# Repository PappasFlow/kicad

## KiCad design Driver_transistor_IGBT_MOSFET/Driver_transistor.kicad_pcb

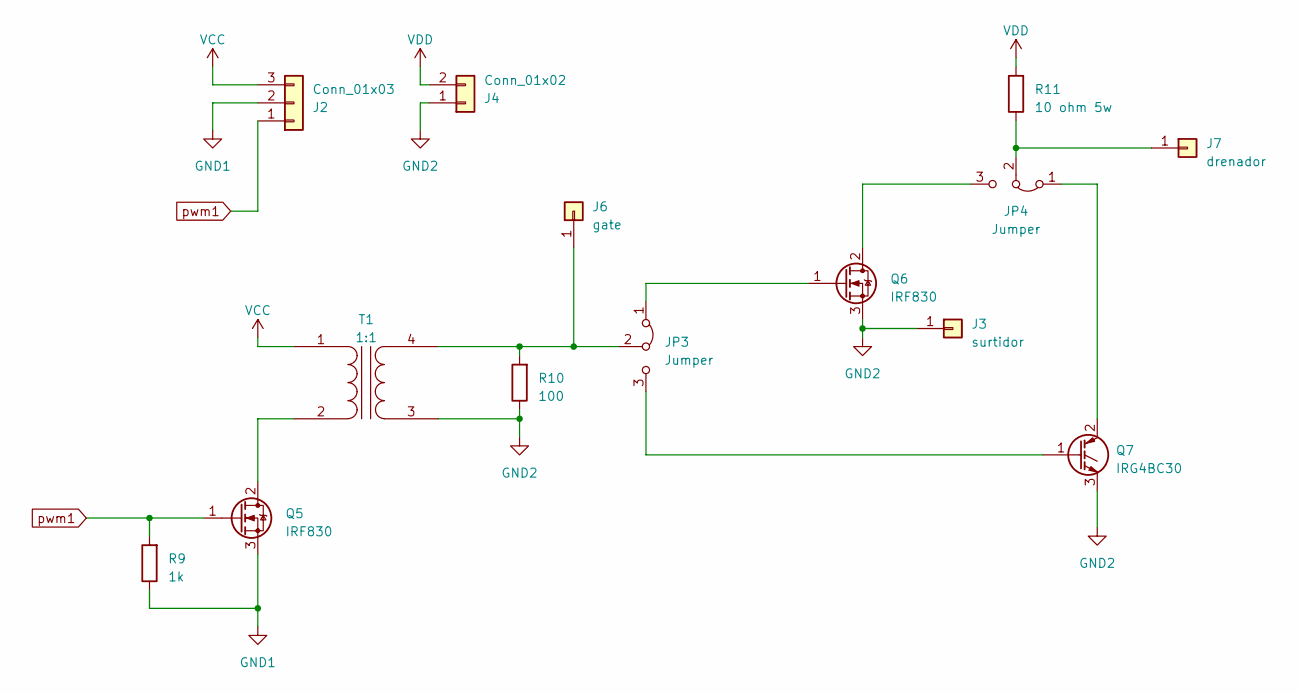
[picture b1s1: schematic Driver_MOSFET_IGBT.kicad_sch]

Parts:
J2: Conn_01x03; Altech_AK300_1x03_P5.00mm_45-Degree
J3: surtidor; PinHeader_1x01_P2.00mm_Vertical
J4: Conn_01x02; Altech_AK300_1x02_P5.00mm_45-Degree
J6: gate; PinHeader_1x01_P2.00mm_Vertical
J7: drenador; PinHeader_1x01_P2.00mm_Vertical
JP3, JP4: Jumper; PinHeader_1x03_P2.00mm_Vertical
Q5, Q6: IRF830; TO-220-3_Vertical
Q7: IRG4BC30; TO-247-3_Vertical
R9: 1k; R_Axial_DIN0207_L6.3mm_D2.5mm_P7.62mm_Horizontal
R10: 100; R_Axial_DIN0207_L6.3mm_D2.5mm_P7.62mm_Horizontal
R11: 10 ohm 5w; R_Axial_Power_L20.0mm_W6.4mm_P22.40mm
T1: 1:1; Transformer_Driver_IGBT_MOSFET

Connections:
GND1: Q5.3 (S), R9.1; also elsewhere on the board
GND2: J3.1, J4.1, Q6.3 (S), Q7.3 (E), R10.1, T1.3 (SA)
unnamed: J6.1, JP3.2 (C), R10.2, T1.4 (SB)
unnamed: J7.1, JP4.2 (C), R11.1
unnamed: JP3.1 (A), Q6.1 (G)
unnamed: JP3.3 (B), Q7.1 (G)
unnamed: JP4.1 (A), Q7.2 (C)
unnamed: JP4.3 (B), Q6.2 (D)
unnamed: Q5.2 (D), T1.2 (AB)
VCC: T1.1 (AA); also elsewhere on the board
VDD: J4.2, R11.2
pwm1: Q5.1 (G), R9.2; also elsewhere on the board

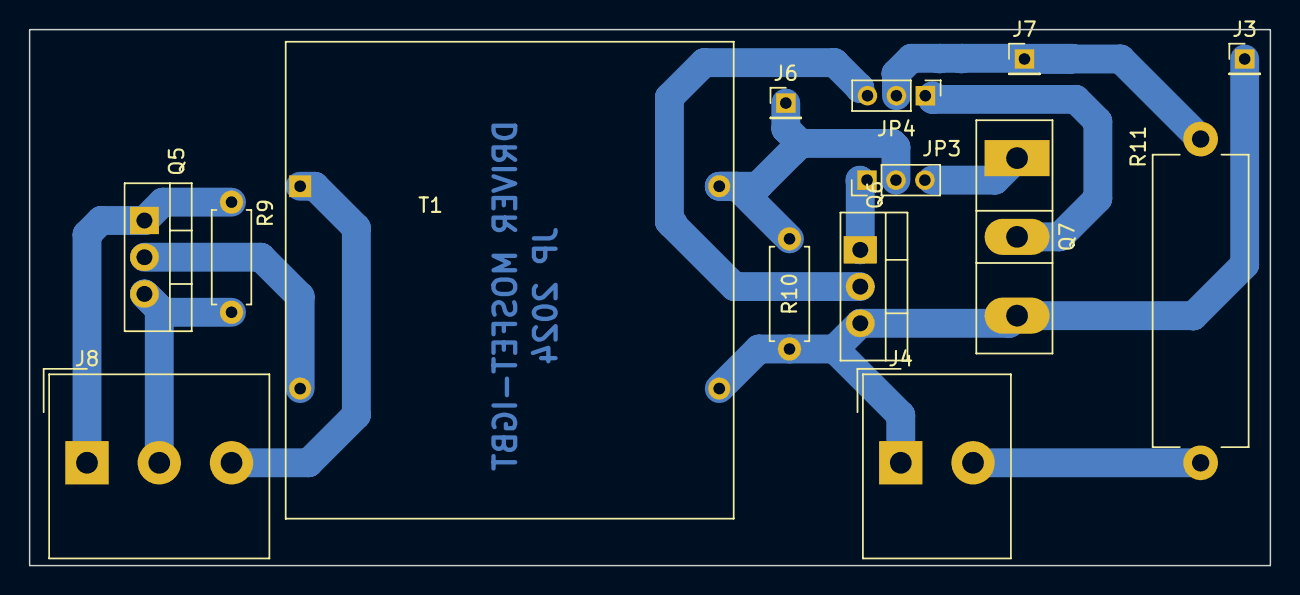
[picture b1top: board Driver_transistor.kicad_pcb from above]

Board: 2 copper layers, 85.9 x 37.1 mm, 14 parts (0 on the bottom side), 12 nets.

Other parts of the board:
J8: Conn_01x03; Altech_AK300_1x03_P5.00mm_45-Degree

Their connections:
GND1: J8.2; also elsewhere on the board
VCC: J8.3; also elsewhere on the board
pwm1: J8.1; also elsewhere on the board

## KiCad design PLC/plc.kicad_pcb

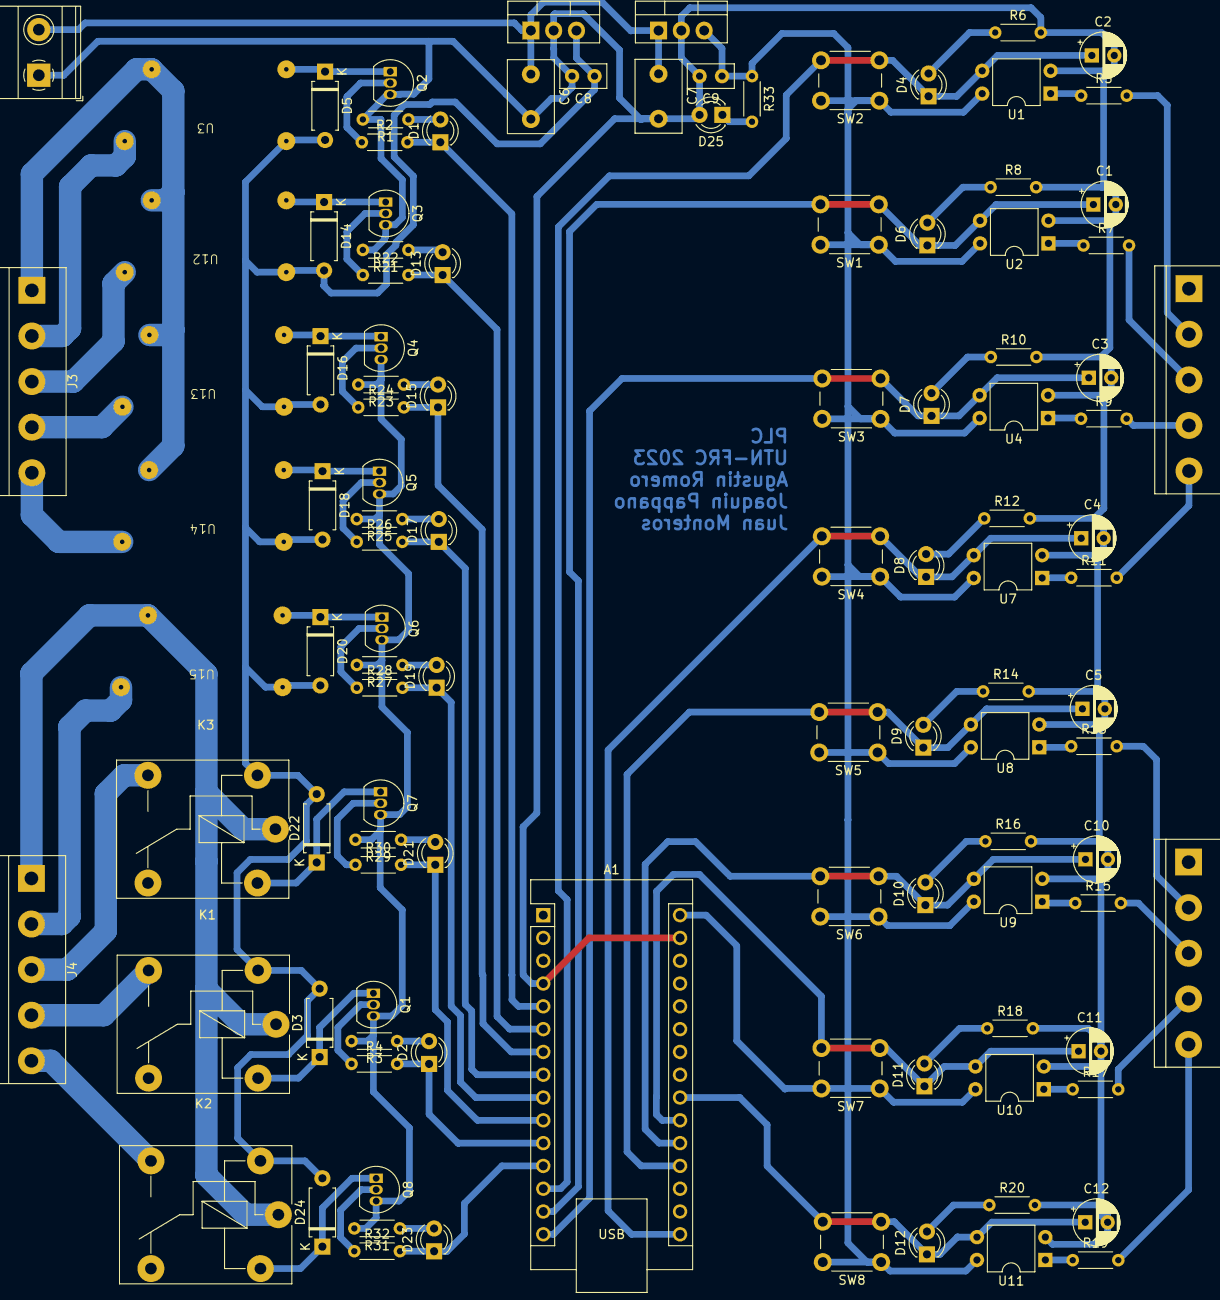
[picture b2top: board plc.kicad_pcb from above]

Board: 2 copper layers, 110 parts (0 on the bottom side), 79 nets.

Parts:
A1: Arduino_Nano_v3.x; Arduino_Nano
C1, C2, C3, C4, C5, C10, C11, C12: 1uF; CP_Radial_D5.0mm_P2.50mm
C6, C7: 0.33uF1; C_Disc_D8.0mm_W5.0mm_P5.00mm
C8, C9: 0.1uF1; C_Disc_D5.0mm_W2.5mm_P2.50mm
D1, D2, D4, D6, D7, D8, D9, D10, D11, D12, D13, D15, D17, D19, D21, D23, D25: LED; LED_D3.0mm
D3, D5, D14, D16, D18, D20, D22, D24: 1N4007; D_A-405_P7.62mm_Horizontal
J1: Conn_in24_0; TerminalBlock_bornier-5_P5.08mm
J2: Conn_in24_1; TerminalBlock_bornier-5_P5.08mm
J3: Conn_rele_0; TerminalBlock_bornier-5_P5.08mm
J4: Conn_rele_1; TerminalBlock_bornier-5_P5.08mm
K1, K2, K3: FINDER-36.11; Relay_SPDT_Finder_36.11
Q1, Q2, Q3, Q4, Q5, Q6, Q7, Q8: BC557; TO-92_Inline
R1, R3, R21, R23, R25, R27, R29, R31: 1K; R_Axial_DIN0204_L3.6mm_D1.6mm_P5.08mm_Horizontal
R2, R4, R22, R24, R26, R28, R30, R32: 10k; R_Axial_DIN0204_L3.6mm_D1.6mm_P5.08mm_Horizontal
R5, R6, R7, R8, R9, R10, R11, R12, R13, R14, R15, R16, R17, R18, R19, R20, R33: 1k; R_Axial_DIN0204_L3.6mm_D1.6mm_P5.08mm_Horizontal
SW1, SW2, SW3, SW4, SW5, SW6, SW7, SW8: SW_PUSH; SW_PUSH_6mm_H5mm
U1, U2, U4, U7, U8, U9, U10, U11: PC817; DIP-4_W7.62mm
U3, U12, U13, U14, U15: RSEIV-JMU
U5: LM7812_TO220; TO-220-3_Vertical
U6: LM7805_TO220; TO-220-3_Vertical
con2: Vin; TerminalBlock_Phoenix_MKDS-1,5-2-5.08_1x02_P5.08mm_Horizont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

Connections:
+5V: A1.30 (VIN), C9.1, R33.1, SW1.1, SW2.1, SW3.1, SW4.1, SW5.1, SW6.1, SW7.1, SW8.1, U1.4, U2.4, U4.4, U6.3 (VO), U7.4, U8.4, U9.4, U10.4, U11.4
+12V: C8.1, D3.2 (K), D5.2 (K), D14.2 (K), D16.2 (K), D18.2 (K), D20.2 (K), D22.2 (K), D24.2 (K), K1.A1, K2.A1, K3.A1, U3.1, U5.3 (VO), U12.1, U13.1, U14.1, U15.1
GND: A1.4 (GND), A1.29 (GND), C1.2, C2.2, C3.2, C4.2, C5.2, C6.2, C7.2, C8.2, C9.2, C10.2, C11.2, C12.2, D25.2 (K), J1.1, J2.1, Q1.3 (E), Q2.3 (E), Q3.3 (E), Q4.3 (E), Q5.3 (E), Q6.3 (E), Q7.3 (E), Q8.3 (E), R1.2, R3.2, R6.2, R8.2, R10.2, R12.2, R14.2, R16.2, R18.2, R20.2, R21.2, R23.2, R25.2, R27.2, R29.2, R31.2, U1.2, U2.2, U4.2, U5.2 (GND), U6.2 (GND), U7.2, U8.2, U9.2, U10.2, U11.2, con2.1
unnamed: D1.2 (K), R1.1
unnamed: D2.2 (K), R3.1
unnamed: D3.1 (A), K1.A2, Q1.1 (C)
unnamed: D4.2 (K), R6.1
unnamed: D5.1 (A), Q2.1 (C), U3.2
unnamed: D6.2 (K), R8.1
unnamed: D7.2 (K), R10.1
unnamed: D8.2 (K), R12.1
unnamed: D9.2 (K), R14.1
unnamed: D10.2 (K), R16.1
unnamed: D11.2 (K), R18.1
unnamed: D12.2 (K), R20.1
unnamed: D13.2 (K), R21.1
unnamed: D14.1 (A), Q3.1 (C), U12.2
unnamed: D15.2 (K), R23.1
unnamed: D16.1 (A), Q4.1 (C), U13.2
unnamed: D17.2 (K), R25.1
unnamed: D18.1 (A), Q5.1 (C), U14.2
unnamed: D19.2 (K), R27.1
unnamed: D20.1 (A), Q6.1 (C), U15.2
unnamed: D21.2 (K), R29.1
unnamed: D22.1 (A), K3.A2, Q7.1 (C)
unnamed: D23.2 (K), R31.1
unnamed: D24.1 (A), K2.A2, Q8.1 (C)
unnamed: D25.1 (A), R33.2
unnamed: Q1.2 (B), R4.1
unnamed: Q2.2 (B), R2.1
unnamed: Q3.2 (B), R22.1
unnamed: Q4.2 (B), R24.1
unnamed: Q5.2 (B), R26.1
unnamed: Q6.2 (B), R28.1
unnamed: Q7.2 (B), R30.1
unnamed: Q8.2 (B), R32.1
unnamed: R5.1, U1.1
unnamed: R7.1, U2.1
unnamed: R9.1, U4.1
unnamed: R11.1, U7.1
unnamed: R13.1, U8.1
unnamed: R15.1, U9.1
unnamed: R17.1, U10.1
unnamed: R19.1, U11.1
Vin: C6.1, C7.1, U5.1 (VI), U6.1 (VI), con2.2 (PM)
in24_0: J1.2, R5.2
in24_1: J1.3, R7.2
in24_2: J1.4, R9.2
in24_3: J1.5, R11.2
in24_4: J2.2, R13.2
in24_5: J2.3, R15.2
in24_6: J2.4, R17.2
in24_7: J2.5, R19.2
in_0: A1.13 (D10), C2.1, D4.1 (A), SW2.2, U1.3
in_1: A1.14 (D11), C1.1, D6.1 (A), SW1.2, U2.3
in_2: A1.15 (D12), C3.1, D7.1 (A), SW3.2, U4.3
in_3: A1.16 (D13), C4.1, D8.1 (A), SW4.2, U7.3
in_4: A1.19 (A0), C5.1, D9.1 (A), SW5.2, U8.3
in_5: A1.20 (A1), C10.1, D10.1 (A), SW6.2, U9.3
in_6: A1.21 (A2), C11.1, D11.1 (A), SW7.2, U10.3
in_7: A1.22 (A3), C12.1, D12.1 (A), SW8.2, U11.3
outR_0: J3.2, U3.3
outR_1: J3.3, U12.3
outR_2: J3.4, U13.3
outR_3: J3.5, U14.3
outR_4: J4.2, U15.3
outR_5: J4.3, K3.14
outR_6: J4.4, K1.14
outR_7: J4.5, K2.14
out_0: A1.5 (D2), D1.1 (A), R2.2
out_1: A1.6 (D3), D13.1 (A), R22.2
out_2: A1.7 (D4), D15.1 (A), R24.2
out_3: A1.8 (D5), D17.1 (A), R26.2
out_4: A1.9 (D6), D19.1 (A), R28.2
out_5: A1.10 (D7), D21.1 (A), R30.2
out_6: A1.11 (D8), D2.1 (A), R4.2
out_7: A1.12 (D9), D23.1 (A), R32.2
pwr_R_0: J3.1, U3.4, U12.4, U13.4, U14.4
pwr_R_1: J4.1, K1.11, K2.11, K3.11, U15.4

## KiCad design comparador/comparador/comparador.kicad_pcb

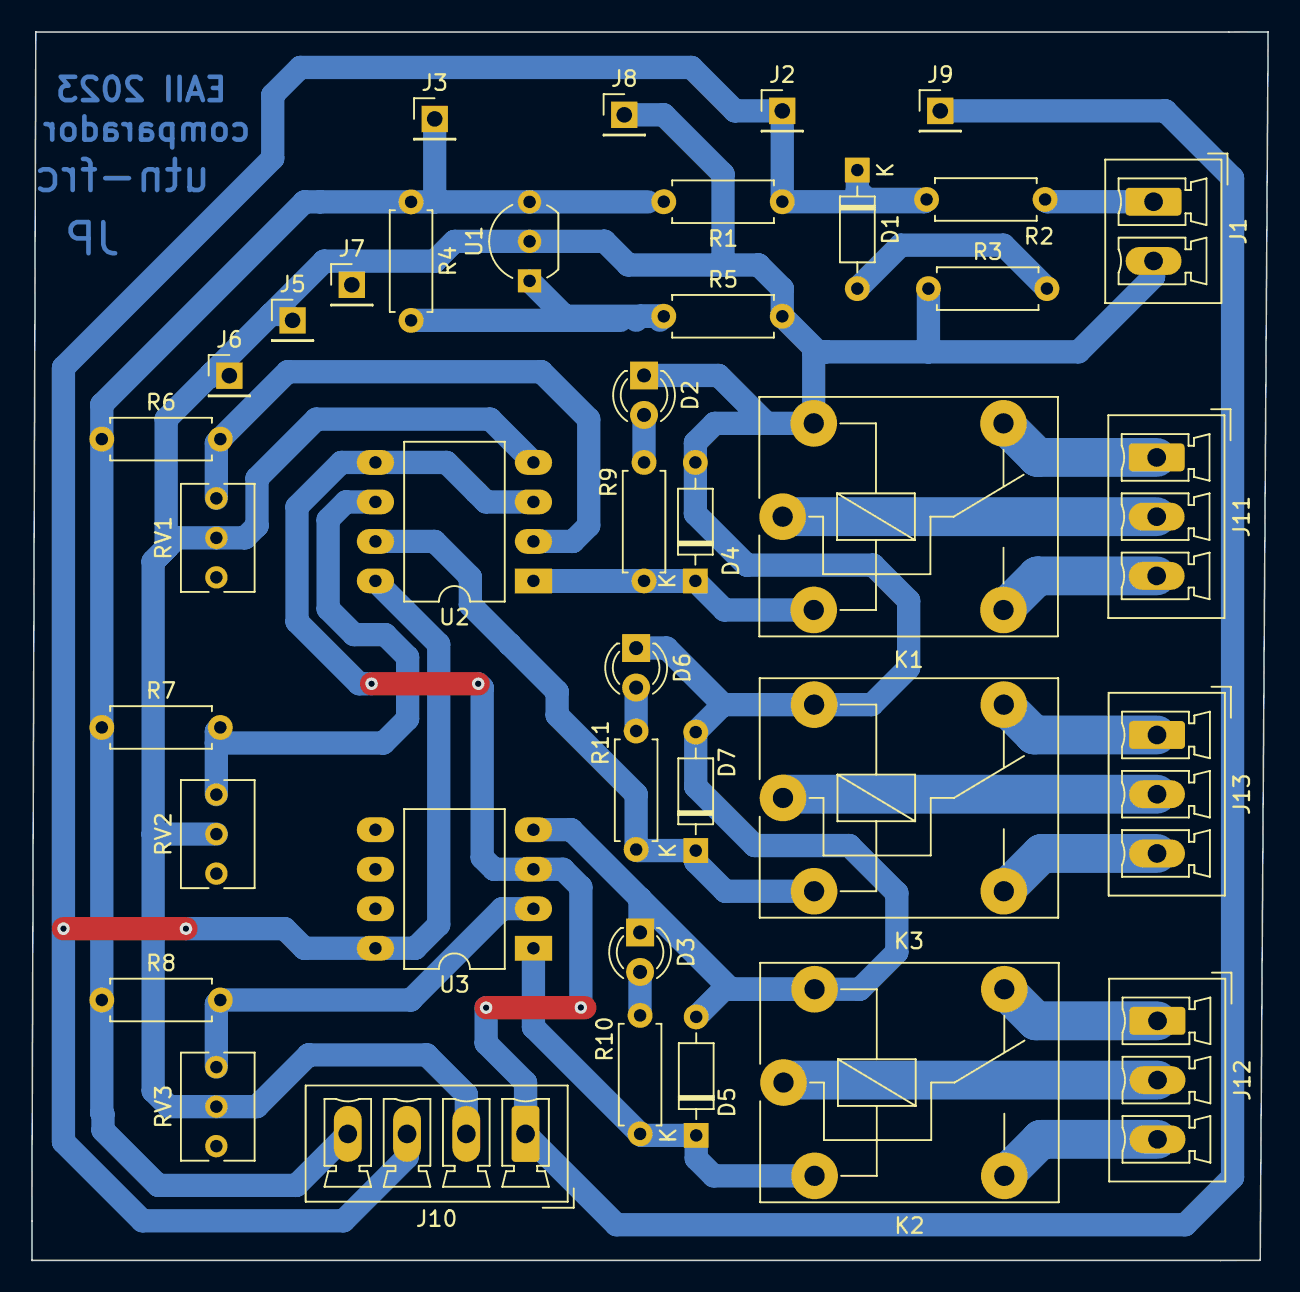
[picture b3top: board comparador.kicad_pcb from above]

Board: 2 copper layers, 79.5 x 79.0 mm, 39 parts (0 on the bottom side), 25 nets.

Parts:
D1: D_Zener; D_DO-35_SOD27_P7.62mm_Horizontal
D2, D3, D6: LED; LED_D3.0mm
D4, D5, D7: D; D_DO-35_SOD27_P7.62mm_Horizontal
J1: alimentacion; PhoenixContact_MCV_1,5_2-G-3.81_1x02_P3.81mm_Vertical
J2: +15; PinHeader_1x01_P2.54mm_Vertical
J3: +5; PinHeader_1x01_P2.54mm_Vertical
J5, J6, J7, J8: GND; PinHeader_1x01_P2.54mm_Vertical
J9: sensor; PinHeader_1x01_P2.54mm_Vertical
J10: exp; PhoenixContact_MCV_1,5_4-G-3.81_1x04_P3.81mm_Vertical
J11, J12, J13: out; PhoenixContact_MCV_1,5_3-G-3.81_1x03_P3.81mm_Vertical
K1, K2, K3: FINDER-36.11; Relay_SPDT_Finder_36.11
R1, R2, R3, R4, R5, R9, R10, R11: R; R_Axial_DIN0207_L6.3mm_D2.5mm_P7.62mm_Horizontal
R6, R7, R8: 1k; R_Axial_DIN0207_L6.3mm_D2.5mm_P7.62mm_Horizontal
RV1, RV2, RV3: 10K; Potentiometer_Bourns_3266Y_Vertical
U1: TL431LP; TO-92_Inline_Wide
U2, U3: TL082; DIP-8_W10.16mm_LongPads

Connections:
+5V: J3.1, J10.4, R1.2, R4.1, R6.1, R7.1, R8.1, U1.3 (K)
+15V: D1.1 (K), J2.1, J10.3, R1.1, R2.2, U2.8 (V+), U3.8 (V+)
GND: D2.1 (K), D3.1 (K), D4.2 (A), D5.2 (A), D6.1 (K), D7.2 (A), J1.2, J5.1, J6.1, J7.1, J8.1, J10.2, K1.A2, K2.A2, K3.A2, R3.1, R5.2, RV1.2, RV2.2, RV3.2, U1.2 (A), U2.4 (V-), U3.4 (V-)
unnamed: D1.2 (A), R3.2
unnamed: D2.2 (A), R9.1
unnamed: D3.2 (A), R10.1
unnamed: D4.1 (K), K1.A1, R9.2, U2.1
unnamed: D5.1 (K), K2.A1, R10.2, U3.1
unnamed: D6.2 (A), R11.1
unnamed: D7.1 (K), K3.A1, R11.2, U2.7
unnamed: J1.1, R2.1
unnamed: J11.1, K1.12
unnamed: J11.2, K1.11
unnamed: J11.3, K1.14
unnamed: J12.1, K2.12
unnamed: J12.2, K2.11
unnamed: J12.3, K2.14
unnamed: J13.1, K3.12
unnamed: J13.2, K3.11
unnamed: J13.3, K3.14
unnamed: R4.2, R5.1, U1.1 (REF)
ldr: J9.1, J10.1, U2.3 (+), U2.5 (+), U3.3 (+)
ref1: R6.2, RV1.1, U2.2 (-)
ref2: R7.2, RV2.1, U2.6 (-)
ref3: R8.2, RV3.1, U3.2 (-)

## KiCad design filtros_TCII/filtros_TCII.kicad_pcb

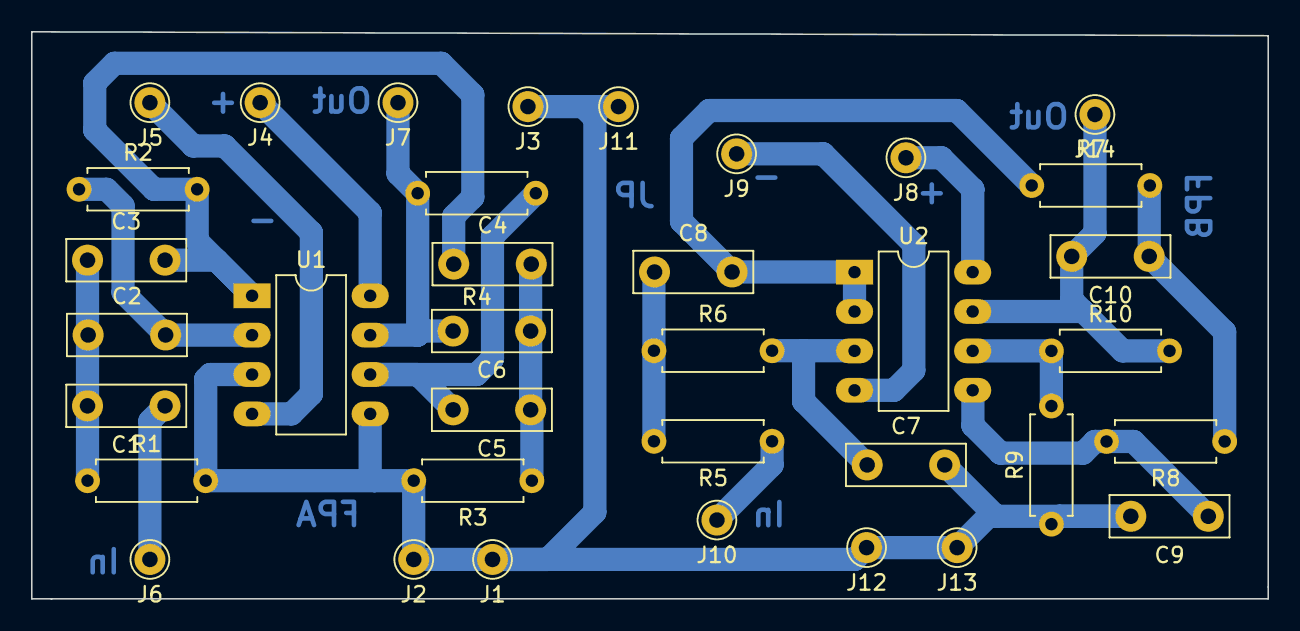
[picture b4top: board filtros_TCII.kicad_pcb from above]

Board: 2 copper layers, 79.8 x 36.6 mm, 36 parts (0 on the bottom side), 20 nets.

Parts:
C1, C2, C3, C4, C5, C6, C7, C8, C9, C10: C; C_Disc_D7.5mm_W2.5mm_P5.00mm
J1, J2, J3, J11, J12, J13: gnd; Pin_D1.0mm_L10.0mm
J4, J8: +15; Pin_D1.0mm_L10.0mm
J5, J9: -15; Pin_D1.0mm_L10.0mm
J6: in_FPA; Pin_D1.0mm_L10.0mm
J7: out_FPA; Pin_D1.0mm_L10.0mm
J10: in_FPB; Pin_D1.0mm_L10.0mm
J14: out_FPB; Pin_D1.0mm_L10.0mm
R1, R2, R3, R4, R5, R6, R7, R8, R9, R10: R; R_Axial_DIN0207_L6.3mm_D2.5mm_P7.62mm_Horizontal
U1, U2: TL082; DIP-8_W7.62mm_LongPads

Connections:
GND: C7.2, C9.2, J1.1, J2.1, J3.1, J11.1, J12.1, J13.1, R1.2, R3.2, R9.1, U1.3 (+), U1.5 (+)
unnamed: C1.2, C2.1, C3.1, R1.1
unnamed: C3.2, C4.1, R2.2, U1.1
unnamed: C4.2, C5.1, C6.1, R3.1
unnamed: C8.1, R5.2, R6.1
unnamed: C10.1, R7.2, R8.1
unnamed: J4.1, U1.8 (V+)
unnamed: J5.1, U1.4 (V-)
unnamed: C1.1, J6.1
unnamed: C6.2, J7.1, R4.2, U1.7
unnamed: J8.1, U2.8 (V+)
unnamed: J9.1, U2.4 (V-)
unnamed: J10.1, R5.1
unnamed: C10.2, J14.1, R10.2, U2.7
unnamed: C2.2, R2.1, U1.2 (-)
unnamed: C5.2, R4.1, U1.6 (-)
unnamed: C7.1, R6.2, U2.3 (+)
unnamed: C8.2, R7.1, U2.1, U2.2 (-)
unnamed: C9.1, R8.2, U2.5 (+)
unnamed: R9.2, R10.1, U2.6 (-)

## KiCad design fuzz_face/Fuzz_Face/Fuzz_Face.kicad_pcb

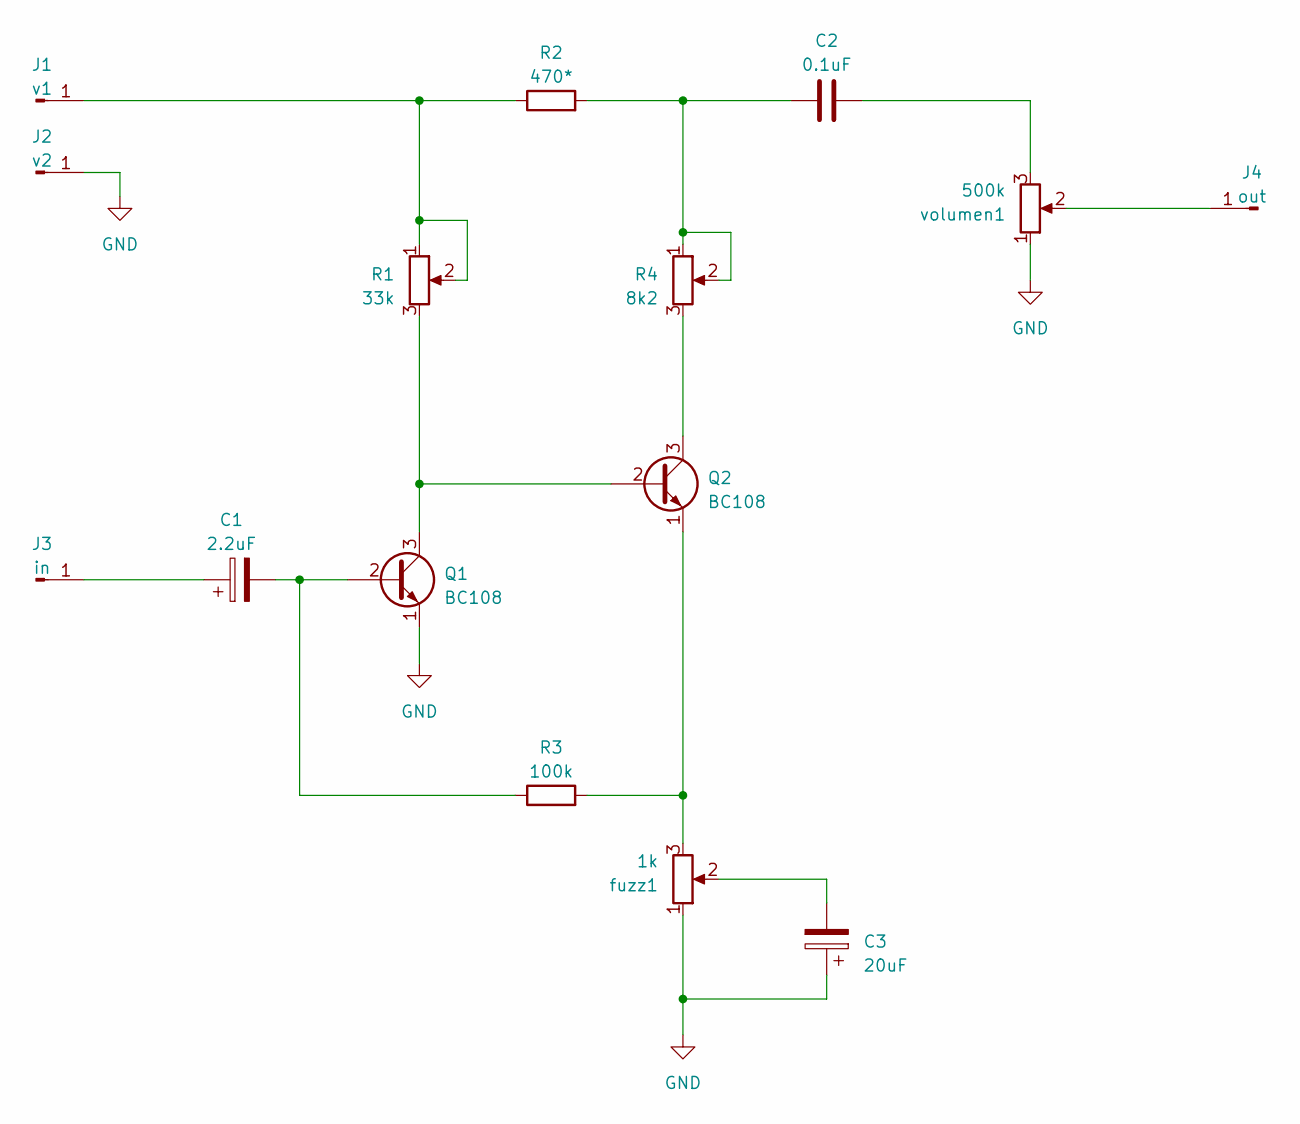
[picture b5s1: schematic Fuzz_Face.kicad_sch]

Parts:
C1: 2.2uF; CP_Radial_D8.0mm_P5.00mm
C2: 0.1uF; CP_Radial_D8.0mm_P5.00mm
C3: 20uF; CP_Radial_D8.0mm_P5.00mm
J1: v1; Pin_D1.3mm_L11.0mm
J2: v2; Pin_D1.3mm_L11.0mm
J3: in; Pin_D1.3mm_L11.0mm
J4: out; Pin_D1.3mm_L11.0mm
Q1, Q2: BC108; TO-18-3
R1: 33k; Potentiometer_Bourns_3266Y_Vertical
R2: 470*; R_Axial_DIN0207_L6.3mm_D2.5mm_P7.62mm_Horizontal
R3: 100k; R_Axial_DIN0207_L6.3mm_D2.5mm_P7.62mm_Horizontal
R4: 8k2; Potentiometer_Bourns_3266Y_Vertical
fuzz1: 1k; Potentiometer_Alps_RK163_Single_Horizontal
volumen1: 500k; Potentiometer_Alps_RK163_Single_Horizontal

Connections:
GND: C3.1, J2.1, Q1.1 (E), fuzz1.1, volumen1.1
unnamed: C2.1, R2.2, R4.1, R4.2
unnamed: C2.2, volumen1.3
unnamed: C3.2, fuzz1.2
unnamed: J1.1, R1.1, R1.2, R2.1
unnamed: C1.1, J3.1
unnamed: J4.1, volumen1.2
unnamed: C1.2, Q1.2 (B), R3.1
unnamed: Q1.3 (C), Q2.2 (B), R1.3
unnamed: Q2.3 (C), R4.3
unnamed: Q2.1 (E), R3.2, fuzz1.3

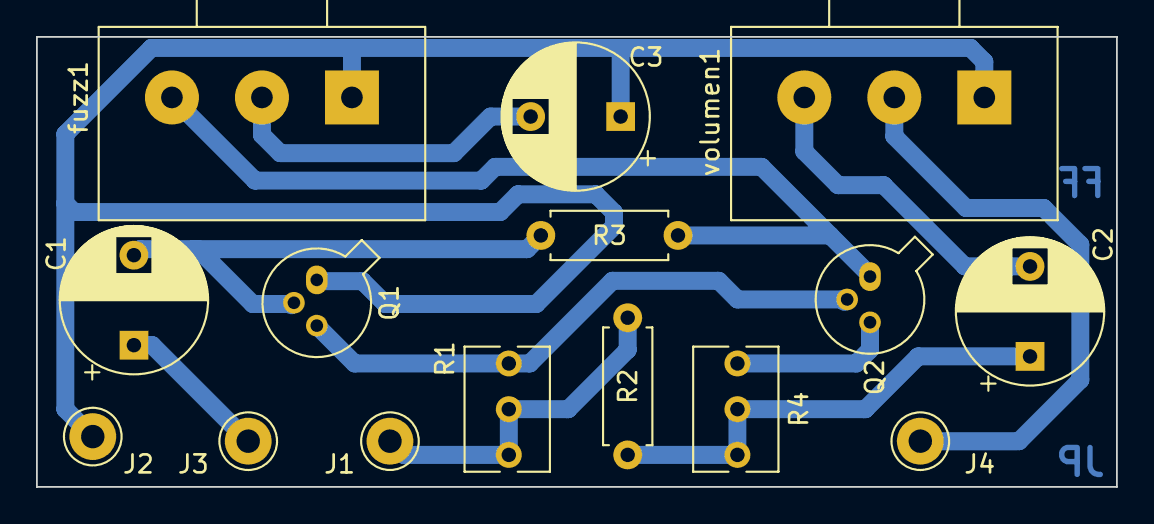
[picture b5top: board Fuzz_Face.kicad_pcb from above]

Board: 2 copper layers, 60.0 x 25.0 mm, 15 parts (0 on the bottom side), 11 nets.

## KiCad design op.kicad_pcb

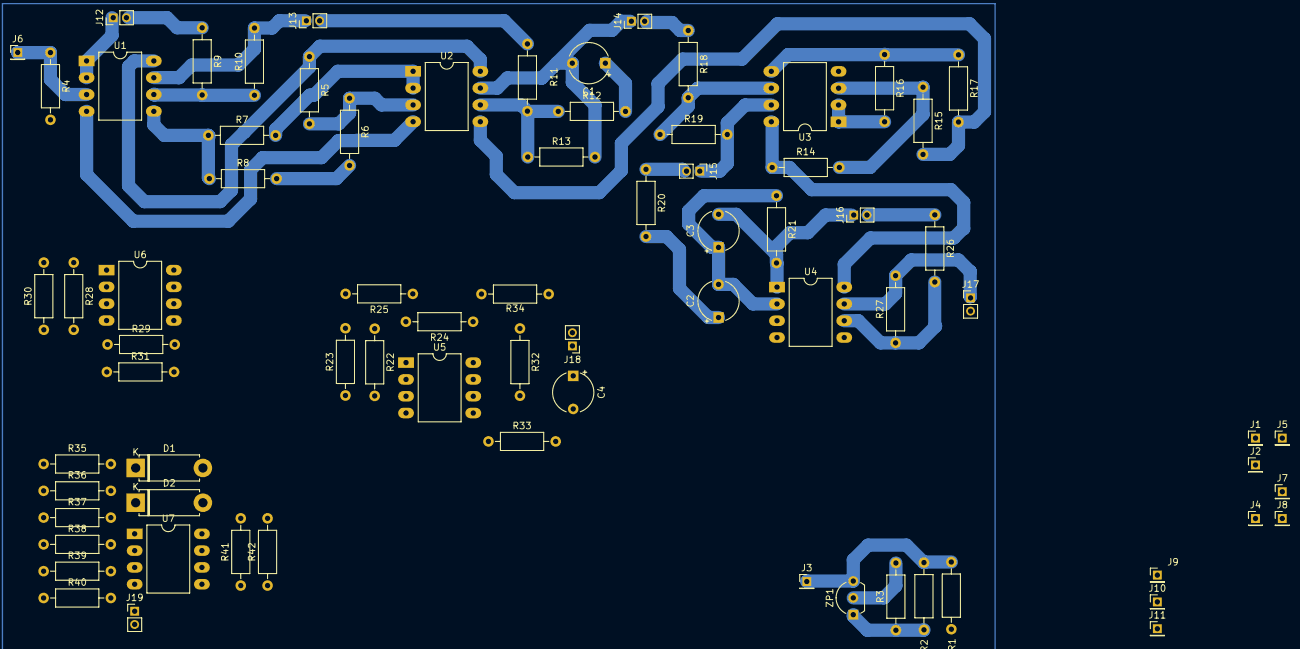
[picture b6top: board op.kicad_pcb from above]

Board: 2 copper layers, 75 parts (0 on the bottom side), 50 nets.

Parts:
C1: 12nF; CP_Radial_Tantal_D6.0mm_P5.00mm
C2: 1nF; CP_Radial_Tantal_D6.0mm_P5.00mm
C3: 56pF; CP_Radial_Tantal_D6.0mm_P5.00mm
C4: 10nF; CP_Radial_Tantal_D6.0mm_P5.00mm
D1, D2: 1N914; D_5W_P10.16mm_Horizontal
J1, J2, J3, J4, J5, J6, J7, J8, J9, J10, J11: Conn_01x01_Pin; PinHeader_1x01_P2.00mm_Vertical
J12, J13, J14, J15, J16, J17, J18, J19: Conn_01x02; PinHeader_1x02_P2.00mm_Vertical
R1, R2, R3, R4: 15k; R_Axial_DIN0207_L6.3mm_D2.5mm_P10.16mm_Horizontal
R5: 18k; R_Axial_DIN0207_L6.3mm_D2.5mm_P10.16mm_Horizontal
R6, R15, R23, R29: 2k; R_Axial_DIN0207_L6.3mm_D2.5mm_P10.16mm_Horizontal
R7, R8, R9, R10, R13, R24, R25, R26, R30, R31, R35, R36, R37, R38, R39, R40, R41, R42: 100k; R_Axial_DIN0207_L6.3mm_D2.5mm_P10.16mm_Horizontal
R11, R16, R18: 10k; R_Axial_DIN0207_L6.3mm_D2.5mm_P10.16mm_Horizontal
R12: 100; R_Axial_DIN0207_L6.3mm_D2.5mm_P10.16mm_Horizontal
R14: 12k; R_Axial_DIN0207_L6.3mm_D2.5mm_P10.16mm_Horizontal
R17, R19: 47k; R_Axial_DIN0207_L6.3mm_D2.5mm_P10.16mm_Horizontal
R20: 4.7K; R_Axial_DIN0207_L6.3mm_D2.5mm_P10.16mm_Horizontal
R21: 63k; R_Axial_DIN0207_L6.3mm_D2.5mm_P10.16mm_Horizontal
R22, R28: 13k; R_Axial_DIN0207_L6.3mm_D2.5mm_P10.16mm_Horizontal
R27: 50k; R_Axial_DIN0207_L6.3mm_D2.5mm_P10.16mm_Horizontal
R32: 56k; R_Axial_DIN0207_L6.3mm_D2.5mm_P10.16mm_Horizontal
R33: 42k; R_Axial_DIN0207_L6.3mm_D2.5mm_P10.16mm_Horizontal
R34: 470; R_Axial_DIN0207_L6.3mm_D2.5mm_P10.16mm_Horizontal
U1, U2, U3, U4, U5, U6, U7: TL082; DIP-8_W10.16mm_LongPads
ZP1: TL431LP; TO-92L_Inline_Wide

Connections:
+15V: J1.1, J2.1, R1.1, R5.1, R14.1, R22.1, R28.1, U1.8 (V+), U2.8 (V+), U3.8 (V+), U4.8 (V+), U5.8 (V+), U6.8 (V+), U7.8 (V+)
-15V: J4.1, J5.1, U1.4 (V-), U2.4 (V-), U3.4 (V-), U4.4 (V-), U5.4 (V-), U6.4 (V-), U7.4 (V-)
GND: J8.1, J9.1, J10.1, J11.1, R3.2, R4.2, R6.2, R8.2, R15.2, R17.2, R23.2, R25.2, R29.2, R31.2, R34.2, R40.1, R41.1, U2.5 (+), U4.3 (+), U6.5 (+), ZP1.2 (A)
INPUT: J6.1, R4.1, U1.3 (+)
unnamed: C1.1, R12.2
unnamed: C2.1, R20.2
unnamed: C4.1, R33.2, U5.7
unnamed: D1.2 (A), R36.2, R38.1
unnamed: D1.1 (K), D2.2 (A), U6.7
unnamed: D2.1 (K), R37.2, U7.3 (+)
unnamed: J3.1, R1.2, R2.1, ZP1.3 (K)
unnamed: J12.1, U1.1, U1.2 (-)
unnamed: J13.1, R10.2, U1.7
unnamed: C1.2, J14.1, R13.2, U2.7
unnamed: J15.1, R19.2, U3.7
unnamed: C3.2, J16.1, R21.2, U4.1
unnamed: J17.1, R27.2, U4.7
unnamed: C4.2, J18.1, R34.1
unnamed: J19.1, R39.2, R40.2, U7.1
unnamed: R7.1, R8.1, U1.5 (+)
unnamed: R9.2, R10.1, U1.6 (-)
unnamed: R5.2, R6.1, U2.3 (+)
unnamed: R7.2, U2.1, U2.2 (-)
unnamed: R11.2, R12.1, R13.1, U2.6 (-)
unnamed: R14.2, R15.1, U3.3 (+)
unnamed: R16.2, U3.1, U3.2 (-)
unnamed: R16.1, R17.1, U3.5 (+)
unnamed: R18.2, R19.1, U3.6 (-)
unnamed: C2.2, C3.1, R21.1, U4.2 (-)
unnamed: R24.1, R25.1, U4.5 (+)
unnamed: R26.2, R27.1, U4.6 (-)
unnamed: R22.2, R23.1, U5.3 (+)
unnamed: R24.2, U5.1, U5.2 (-)
unnamed: R30.1, R31.1, U5.5 (+)
unnamed: R32.2, R33.1, U5.6 (-)
unnamed: R28.2, R29.1, U6.3 (+)
unnamed: R30.2, U6.1, U6.2 (-)
unnamed: R35.2, R36.1, R37.1, U6.6 (-)
unnamed: R38.2, R39.1, U7.2 (-)
unnamed: R41.2, R42.1, U7.6 (-)
unnamed: R2.2, R3.1, ZP1.1 (REF)
out: J7.1, R42.2, U7.7
out_E1: J12.2, R9.1
out_E2: J13.2, R11.1
out_E3: J14.2, R18.1
out_E4: J15.2, R20.1
out_E5: J16.2, R26.1
out_E6: J17.2, R32.1
out_E7: J18.2, R35.1
out_E8: J19.2, U7.5 (+)

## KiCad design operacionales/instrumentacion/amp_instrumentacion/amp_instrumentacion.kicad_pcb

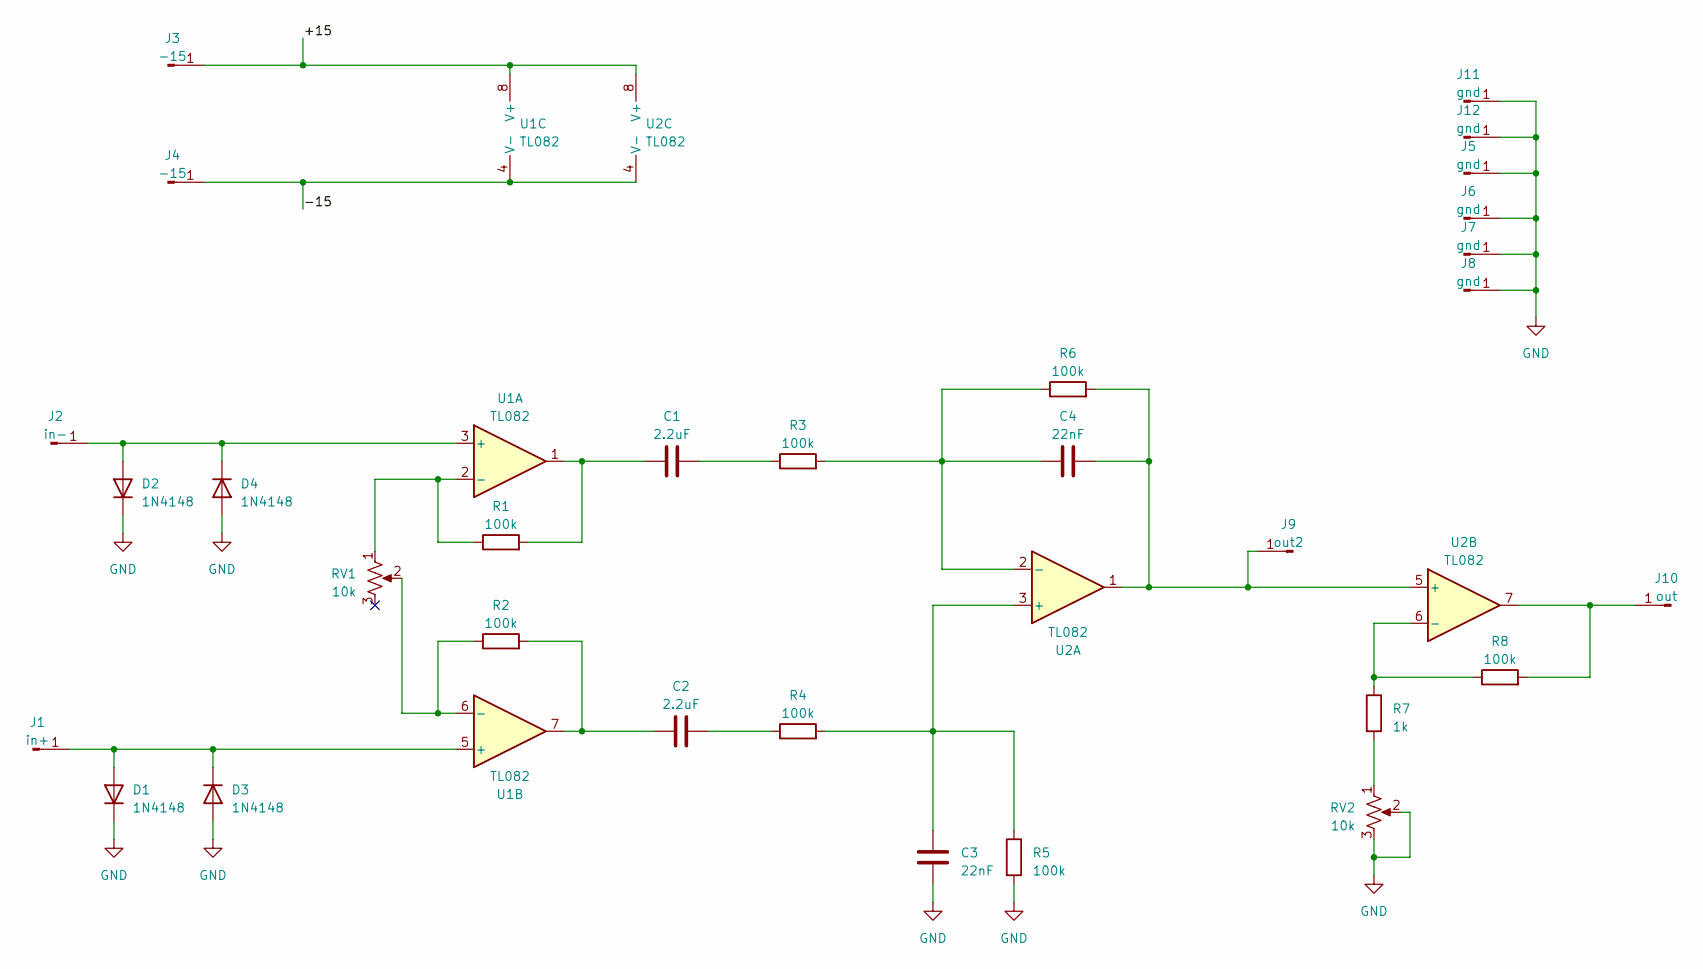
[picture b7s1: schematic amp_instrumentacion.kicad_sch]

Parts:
C1, C2: 2.2uF; CP_Radial_D5.0mm_P2.50mm
C3, C4: 22nF; CP_Radial_D5.0mm_P2.50mm
D1, D2, D3, D4: 1N4148; D_DO-35_SOD27_P7.62mm_Horizontal
J1: in+; Pin_D1.0mm_L10.0mm
J2: in-; Pin_D1.0mm_L10.0mm
J3, J4: -15; Pin_D1.0mm_L10.0mm
J5, J6, J7, J8, J11, J12: gnd; Pin_D1.0mm_L10.0mm
J9: out2; Pin_D1.0mm_L10.0mm
J10: out; Pin_D1.0mm_L10.0mm
R1, R2, R3, R4, R5, R6, R8: 100k; R_Axial_DIN0207_L6.3mm_D2.5mm_P7.62mm_Horizontal
R7: 1k; R_Axial_DIN0207_L6.3mm_D2.5mm_P7.62mm_Horizontal
RV1, RV2: 10k; Potentiometer_Bourns_3266Y_Vertical
U1, U2: TL082; DIP-8_W10.16mm_LongPads

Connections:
/+15: J3.1, U1.8 (V+), U2.8 (V+)
/-15: J4.1, U1.4 (V-), U2.4 (V-)
GND: C3.2, D1.1 (K), D2.1 (K), D3.2 (A), D4.2 (A), J5.1, J6.1, J7.1, J8.1, J11.1, J12.1, R5.2, RV2.2, RV2.3
unnamed: C1.1, R3.1
unnamed: C1.2, R1.2, U1.1
unnamed: C2.1, R2.2, U1.7
unnamed: C2.2, R4.1
unnamed: D1.2 (A), D3.1 (K), J1.1, U1.5 (+)
unnamed: D2.2 (A), D4.1 (K), J2.1, U1.3 (+)
unnamed: C4.1, J9.1, R6.2, U2.1, U2.5 (+)
unnamed: J10.1, R8.2, U2.7
unnamed: R7.2, RV2.1
unnamed: R1.1, RV1.1, U1.2 (-)
unnamed: R2.1, RV1.2, U1.6 (-)
unnamed: C3.1, R4.2, R5.1, U2.3 (+)
unnamed: C4.2, R3.2, R6.1, U2.2 (-)
unnamed: R7.1, R8.1, U2.6 (-)

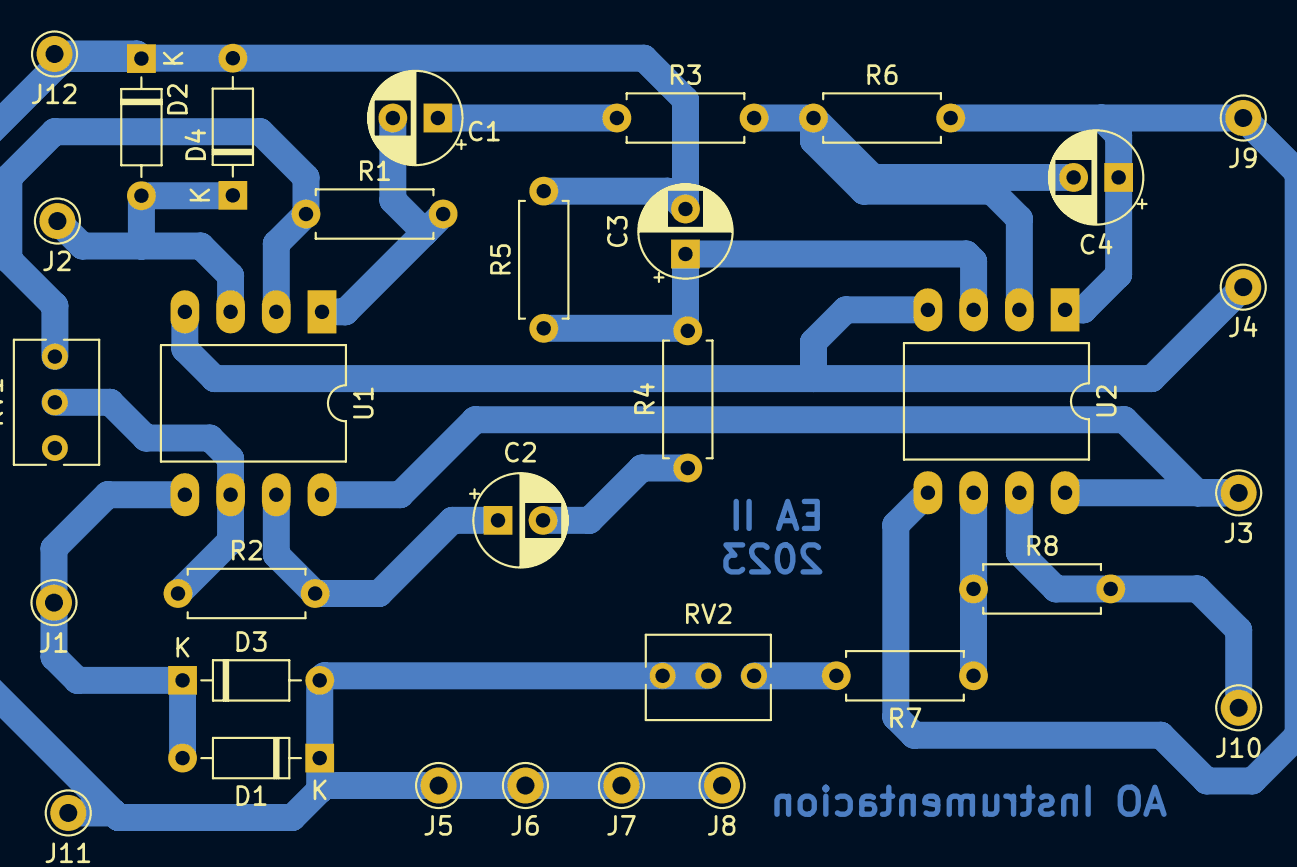
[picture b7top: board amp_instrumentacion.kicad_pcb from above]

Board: 2 copper layers, 32 parts (0 on the bottom side), 17 nets.
